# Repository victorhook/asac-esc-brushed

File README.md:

# **A** **S**imple **A**nd **C**ool brushed ESC
Why do cool fpv drones pretty much always use brushless motors? Well, because they are really good. BUT, they are quite expensive, and brushless ESCs are also quite expensive, since they require somewhat complex hardware and firmware. Thus, this project aims to make a simple and cool ESC that can be used for drones with *brushed* motors. Let's see how this goes!

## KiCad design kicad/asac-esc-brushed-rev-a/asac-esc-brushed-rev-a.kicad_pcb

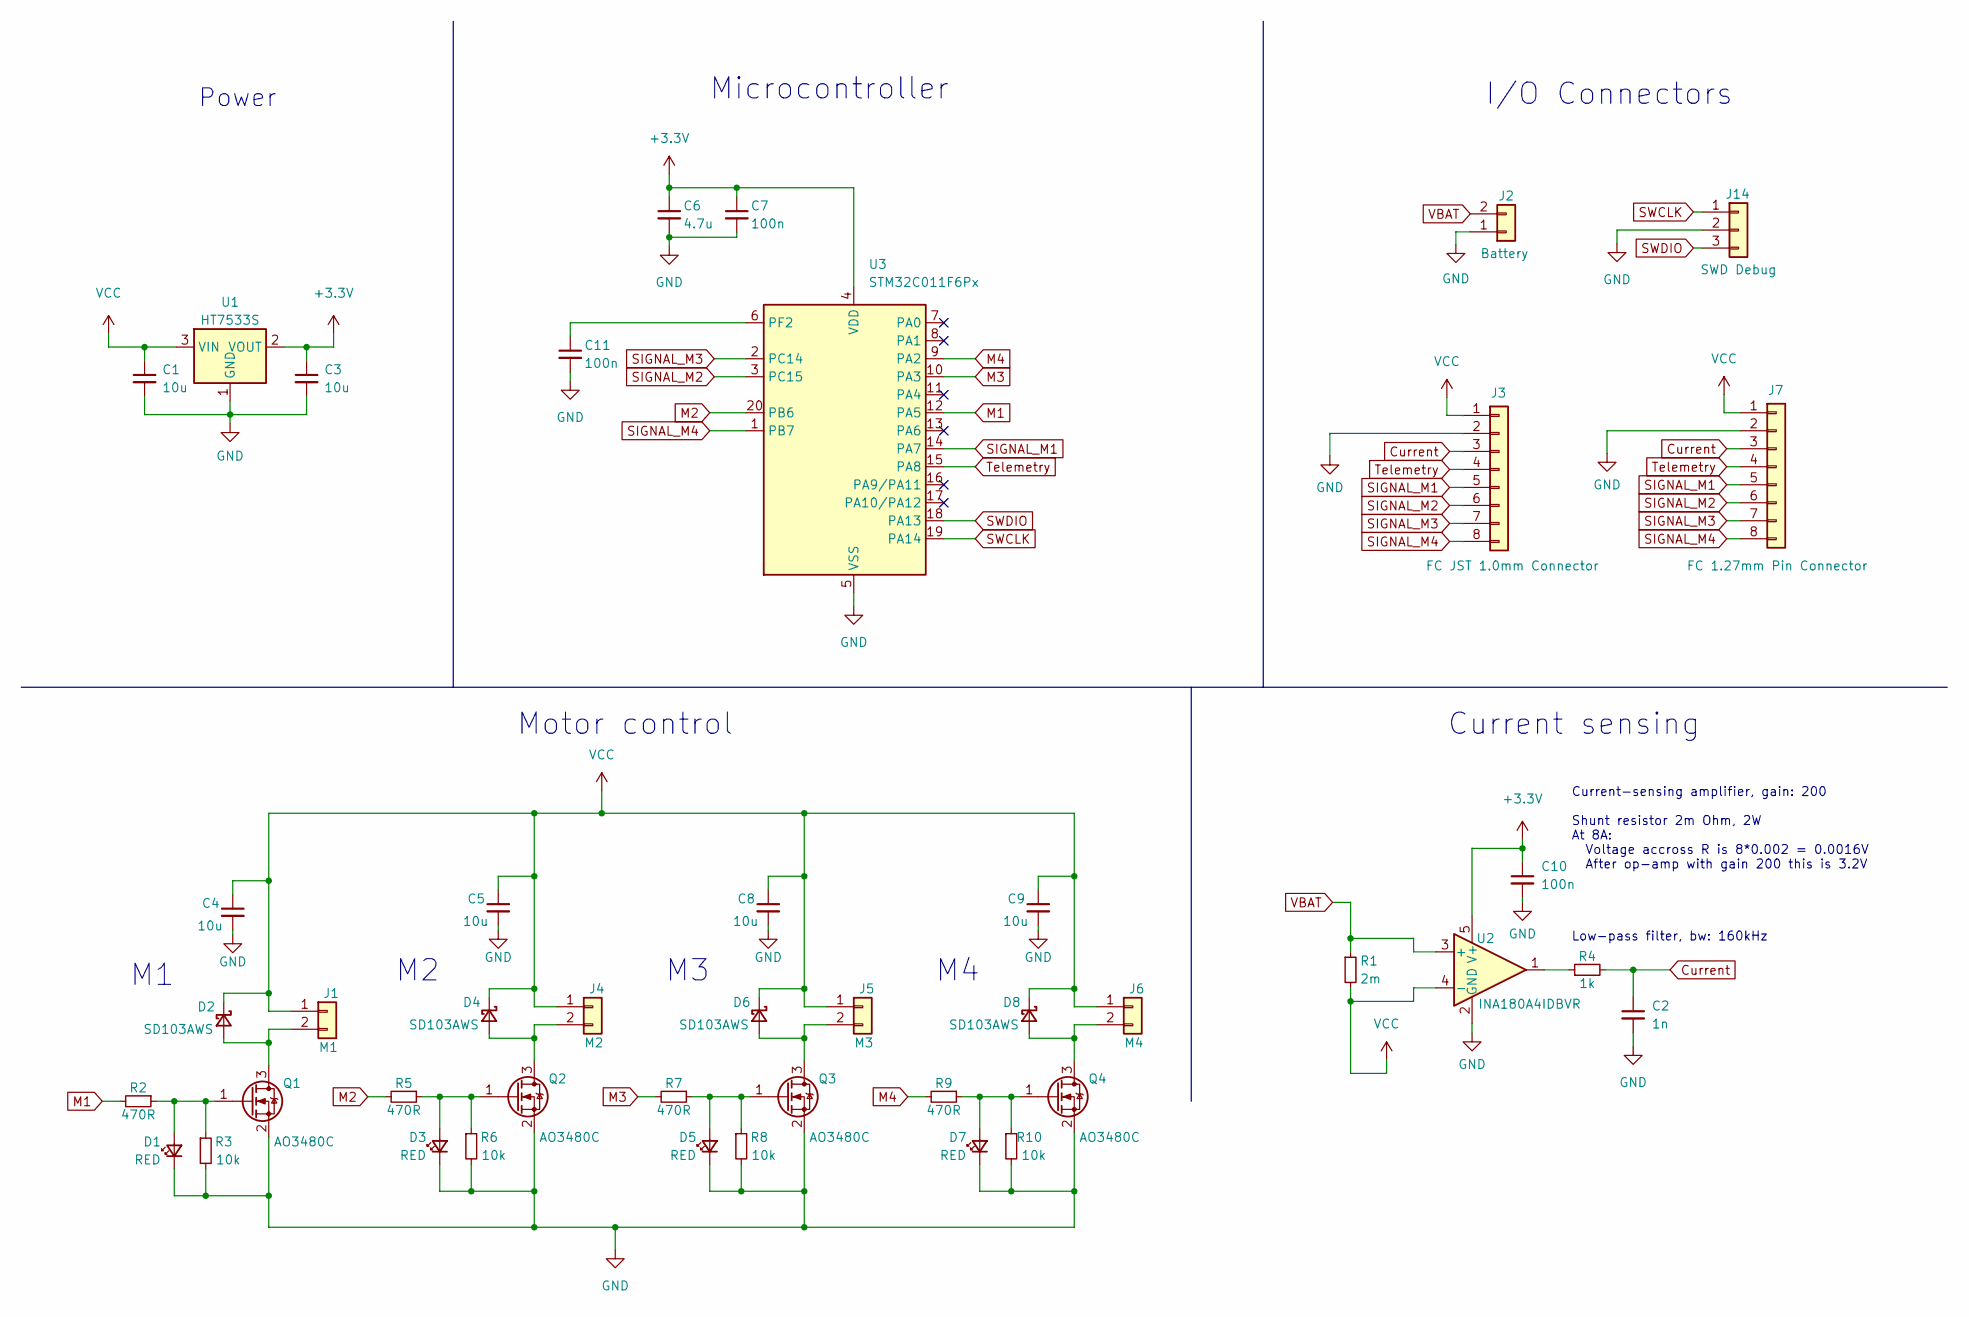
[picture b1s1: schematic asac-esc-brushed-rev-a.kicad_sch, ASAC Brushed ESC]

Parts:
C1, C3, C4, C5, C8, C9: 10u; C_0805_2012Metric
C2: 1n; C_0402_1005Metric
C6: 4.7u; C_0603_1608Metric
C7, C10, C11: 100n; C_0402_1005Metric
D1, D3, D5, D7: RED; LED_0603_1608Metric
D2: SD103AWS; D_SOD-323; MPN C2828423
D4, D6, D8: SD103AWS; D_SOD-323
J1: M1; Conn_01x02_VBAT_one_round
J2: Battery; Conn_01x02_VBAT_BIG
J3: FC JST 1.0mm Connector; JST_SHL_SM08B-SHLS-TF_1x08-1MP_P1.00mm_Horizontal
J4: M2; Conn_01x02_VBAT_one_round
J5: M3; Conn_01x02_VBAT_one_round
J6: M4; Conn_01x02_VBAT_one_round
J7: FC 1.27mm Pin Connector; PinHeader_1x08_P1.27mm_Vertical
J14: SWD Debug; PinHeader_1x03_P1.27mm_Vertical
Q1: AO3480C; SOT-23; MPN C188337
Q2, Q3, Q4: AO3480C; SOT-23
R1: 2m; R_0805_2012Metric
R2, R5, R7, R9: 470R; R_0402_1005Metric
R3, R6, R8, R10: 10k; R_0402_1005Metric
R4: 1k; R_0402_1005Metric
U1: HT7533S; SOT-23-3; MPN C347215
U2: INA180A4IDBVR; SOT-23-5; MPN C188337
U3: STM32C011F6Px; TSSOP-20_4.4x6.5mm_P0.65mm; MPN C5456198

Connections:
+3.3V: C3.1, C6.1, C7.1, C10.1, U1.2 (VOUT), U2.5 (V+), U3.4 (VDD)
Current: C2.1, J3.3, J7.3, R4.2
GND: C1.2, C2.2, C3.2, C4.2, C5.2, C6.2, C7.2, C8.2, C9.2, C10.2, C11.2, D1.1 (K), D3.1 (K), D5.1 (K), D7.1 (K), J2.1, J3.2, J7.2, J14.2, Q1.2 (S), Q2.2 (S), Q3.2 (S), Q4.2 (S), R3.2, R6.2, R8.2, R10.2, U1.1 (GND), U2.2 (GND), U3.5 (VSS)
M1: R2.2, U3.12 (PA5)
M2: R5.2, U3.20 (PB6)
M3: R7.2, U3.10 (PA3)
M4: R9.2, U3.9 (PA2)
unnamed: C11.1, U3.6 (PF2)
unnamed: D1.2 (A), Q1.1 (G), R2.1, R3.1
unnamed: D2.2 (A), J1.2, Q1.3 (D)
unnamed: D3.2 (A), Q2.1 (G), R5.1, R6.1
unnamed: D4.2 (A), J4.2, Q2.3 (D)
unnamed: D5.2 (A), Q3.1 (G), R7.1, R8.1
unnamed: D6.2 (A), J5.2, Q3.3 (D)
unnamed: D7.2 (A), Q4.1 (G), R9.1, R10.1
unnamed: D8.2 (A), J6.2, Q4.3 (D)
unnamed: R4.1, U2.1
SIGNAL_M1: J3.5, J7.5, U3.14 (PA7)
SIGNAL_M2: J3.6, J7.6, U3.3 (PC15)
SIGNAL_M3: J3.7, J7.7, U3.2 (PC14)
SIGNAL_M4: J3.8, J7.8, U3.1 (PB7)
SWCLK: J14.1, U3.19 (PA14)
SWDIO: J14.3, U3.18 (PA13)
Telemetry: J3.4, J7.4, U3.15 (PA8)
VBAT: J2.2, R1.1, U2.3 (+)
VCC: C1.1, C4.1, C5.1, C8.1, C9.1, D2.1 (K), D4.1 (K), D6.1 (K), D8.1 (K), J1.1, J3.1, J4.1, J5.1, J6.1, J7.1, R1.2, U1.3 (VIN), U2.4 (-)

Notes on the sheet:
Current sensing
Low-pass filter, bw: 160kHz
I/O Connectors
Power
Motor control
Current-sensing amplifier, gain: 200 Shunt resistor 2m Ohm, 2W At 8A: Voltage accross R is 8*0.002 = 0.0016V After op-amp with gain 200 this is 3.2V
Microcontroller

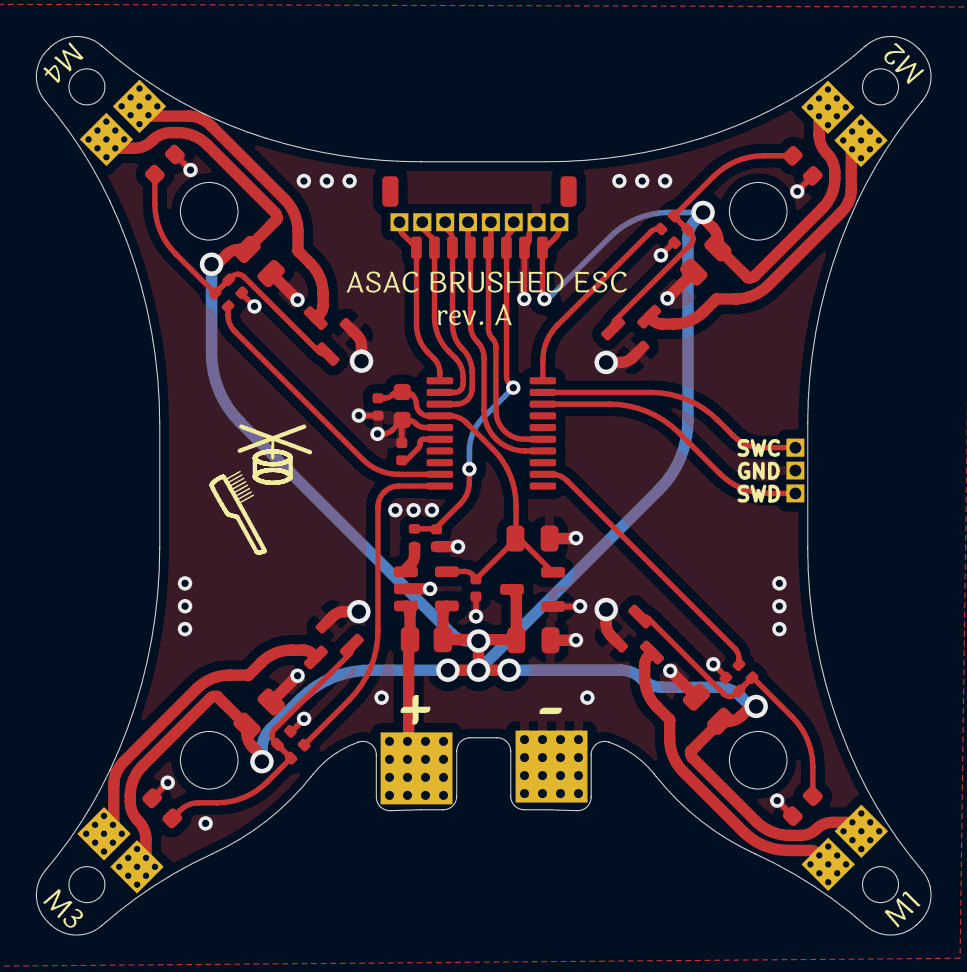
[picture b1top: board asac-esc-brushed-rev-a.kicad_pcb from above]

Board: 2 copper layers, 49.7 x 49.9 mm, 44 parts (0 on the bottom side), 26 nets.

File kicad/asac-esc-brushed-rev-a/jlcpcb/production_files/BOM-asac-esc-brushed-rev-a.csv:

Comment,Designator,Footprint,LCSC
470R,R9,R_0402_1005Metric,
RED,D7,LED_0603_1608Metric,
RED,D1,LED_0603_1608Metric,
AO3480C,Q1,SOT-23,
470R,R2,R_0402_1005Metric,
INA180A4IDBVR,U2,SOT-23-5,
STM32C011F6Px,U3,TSSOP-20_4.4x6.5mm_P0.65mm,
SD103AWS,D6,D_SOD-323,
AO3480C,Q4,SOT-23,
AO3480C,Q3,SOT-23,
10k,R3,R_0402_1005Metric,
2m,R1,R_0805_2012Metric,
SD103AWS,D8,D_SOD-323,
100n,C7,C_0402_1005Metric,
10u,C8,C_0805_2012Metric,
470R,R7,R_0402_1005Metric,
AO3480C,Q2,SOT-23,
10u,C3,C_0805_2012Metric,
SD103AWS,D4,D_SOD-323,
100n,C10,C_0402_1005Metric,
1k,R4,R_0402_1005Metric,
470R,R5,R_0402_1005Metric,
100n,C11,C_0402_1005Metric,
10k,R6,R_0402_1005Metric,
RED,D5,LED_0603_1608Metric,
1n,C2,C_0402_1005Metric,
10u,C1,C_0805_2012Metric,
4.7u,C6,C_0603_1608Metric,
FC JST 1.0mm Connector,J3,JST_SHL_SM08B-SHLS-TF_1x08-1MP_P1.00mm_Horizontal,
10u,C5,C_0805_2012Metric,
10u,C4,C_0805_2012Metric,
10k,R10,R_0402_1005Metric,
SD103AWS,D2,D_SOD-323,
RED,D3,LED_0603_1608Metric,
10u,C9,C_0805_2012Metric,
HT7533S,U1,SOT-23-3,
10k,R8,R_0402_1005Metric,

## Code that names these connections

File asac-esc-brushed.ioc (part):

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Mcu.Name=STM32C011F(4-6)Px
Mcu.Package=TSSOP20
Mcu.UserName=STM32C011F6Px
PA13.Mode=Serial_Wire
PA13.Signal=DEBUG_SWDIO
PA14-BOOT0.Mode=Serial_Wire
PA14-BOOT0.Signal=DEBUG_SWCLK
PA2.Signal=S_TIM1_CH3
PA3.Signal=S_TIM1_CH4
PA5.Signal=S_TIM1_CH1
PA7.Signal=GPIO_Input
PA8.Mode=Half_duplex(single_wire_mode)
PA8.Signal=USART2_TX
PB6.Signal=S_TIM1_CH2
PB7.Signal=GPIO_Input
PC14-OSCX_IN\ (PC14).Signal=GPIO_Input
PC15-OSCX_OUT\ (PC15).Signal=GPIO_Input
RCC.HSE_VALUE=8000000
RCC.SYSCLKFreq_VALUE=12000000
board=custom

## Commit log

2023-09-23 Finished rev A schematic, layout and routing
    All that is left now is to add some graphics!
2023-09-24 Added initial STM32CubeMX config
2023-09-24 Rev. A ready for order!
